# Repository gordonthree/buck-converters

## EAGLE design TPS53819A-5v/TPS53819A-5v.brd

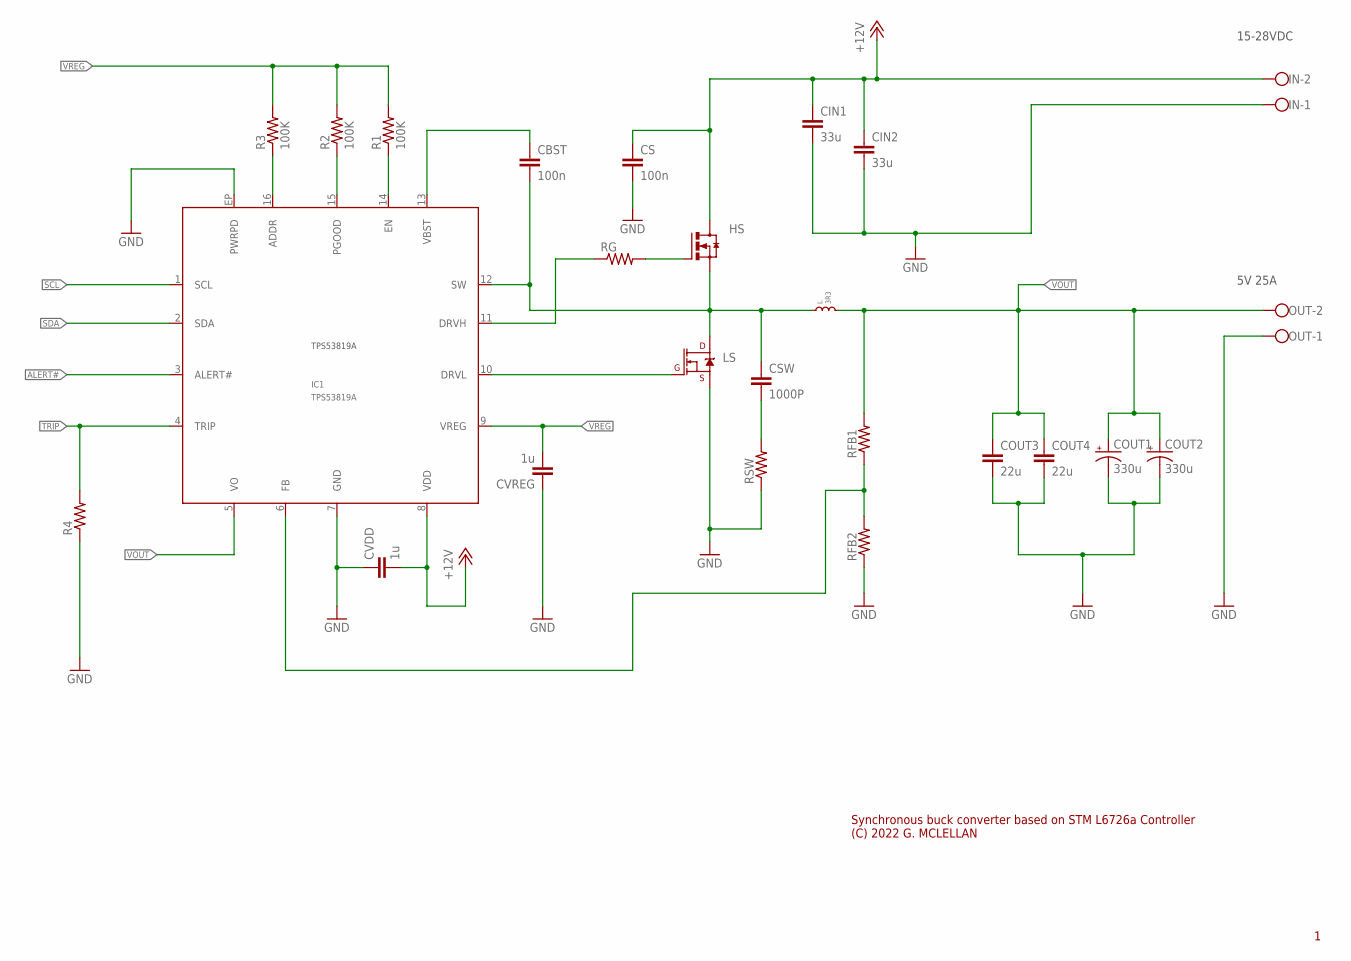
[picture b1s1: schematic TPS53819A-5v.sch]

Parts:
CBST: 100n; C0603
CIN1, CIN2: 33u; C2220K
COUT1, COUT2: 330u; SANYO-OSCON_SMD_C6
COUT3, COUT4: 22u; C1206
CS: 100n; C0805
CSW: 1000P; C0603
CVDD: 1u; C0805
CVREG: 1u; C0603
HS: N_MOSFET_POWERSO8; POWERSO8
IC1: TPS53819A; QFN-16
IN: W237-102
L: 3R3; XAL1010
LS: MOSFET-NCH-FDS6630A; SO08
OUT: W237-102
R1, R2, R3: 100K; R0603
R4: R-US_R0603; R0603
RFB1, RFB2: R-US_R0805; R0805
RG: R-US_R0603; R0603
RSW: R-US_R0603; R0603

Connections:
ADDR: IC1.16 (ADDR), R3.1
ALERT#: IC1.3 (ALERT#)
DRVH: HS.4 (G), RG.2
DRVH`: IC1.11 (DRVH), RG.1
DRVL: IC1.10 (DRVL), LS.4 (G)
EN: IC1.14 (EN), R1.1
FB: IC1.6 (FB), RFB1.1, RFB2.2
GND: CIN1.2, CIN2.2, COUT1.-, COUT2.-, COUT3.2, COUT4.2, CS.2, CVDD.1, CVREG.1, IC1.7 (GND), IC1.EP (PWRPD), IN.1, LS.1 (S), LS.2 (S), LS.3 (S), OUT.1, R4.1, RFB2.1, RSW.1
unnamed: CSW.2, RSW.2
PGOOD: IC1.15 (PGOOD), R2.1
SCL: IC1.1 (SCL)
SDA: IC1.2 (SDA)
SW: CBST.2, CSW.1, HS.1 (S), HS.2 (S), HS.3 (S), IC1.12 (SW), L.P$1 (1), LS.5 (D), LS.6 (D), LS.7 (D), LS.8 (D)
TRIP: IC1.4 (TRIP), R4.2
VBST: CBST.1, IC1.13 (VBST)
VDD: CIN1.1, CIN2.1, CS.1, CVDD.2, HS.5 (D), HS.6 (D), HS.7 (D), HS.8 (D), HS.PAD (D), IC1.8 (VDD), IN.2
VOUT: COUT1.+, COUT2.+, COUT3.1, COUT4.1, IC1.5 (VO), L.P$2 (2), OUT.2, RFB1.2
VREG: CVREG.2, IC1.9 (VREG), R1.2, R2.2, R3.2

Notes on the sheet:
Synchronous buck converter based on STM L6726a Controller (C) 2022 G. MCLELLAN
15-28VDC
5V 25A

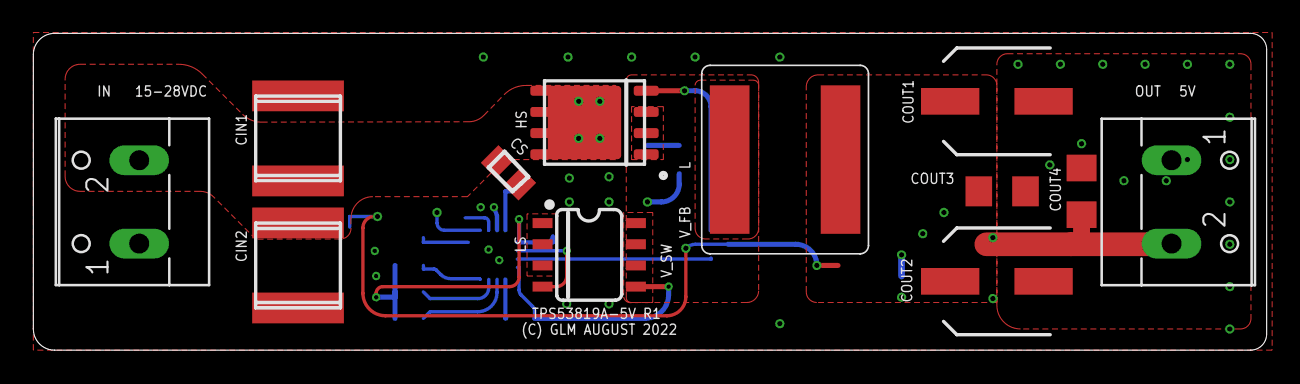
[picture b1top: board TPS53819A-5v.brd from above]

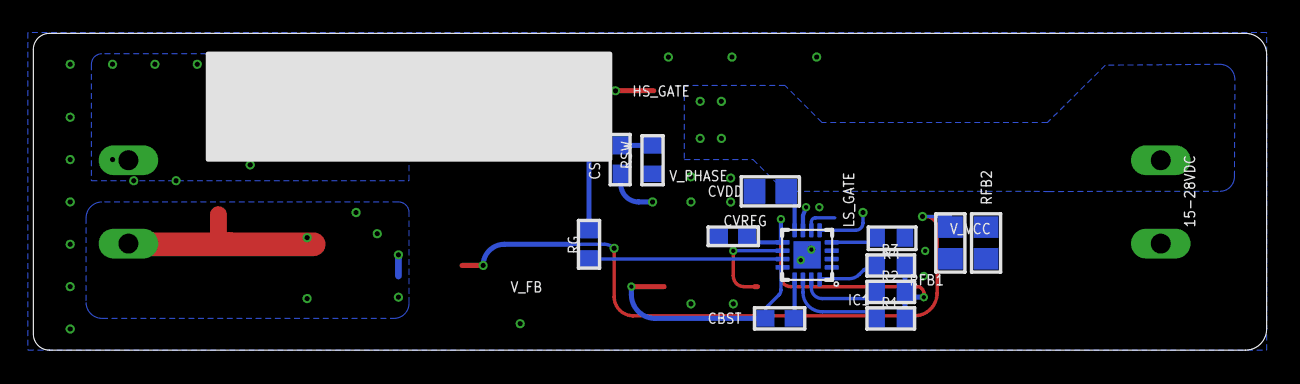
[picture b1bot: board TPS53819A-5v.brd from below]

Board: 2 copper layers, 74.0 x 19.0 mm, 25 parts (13 on the bottom side), 15 nets.

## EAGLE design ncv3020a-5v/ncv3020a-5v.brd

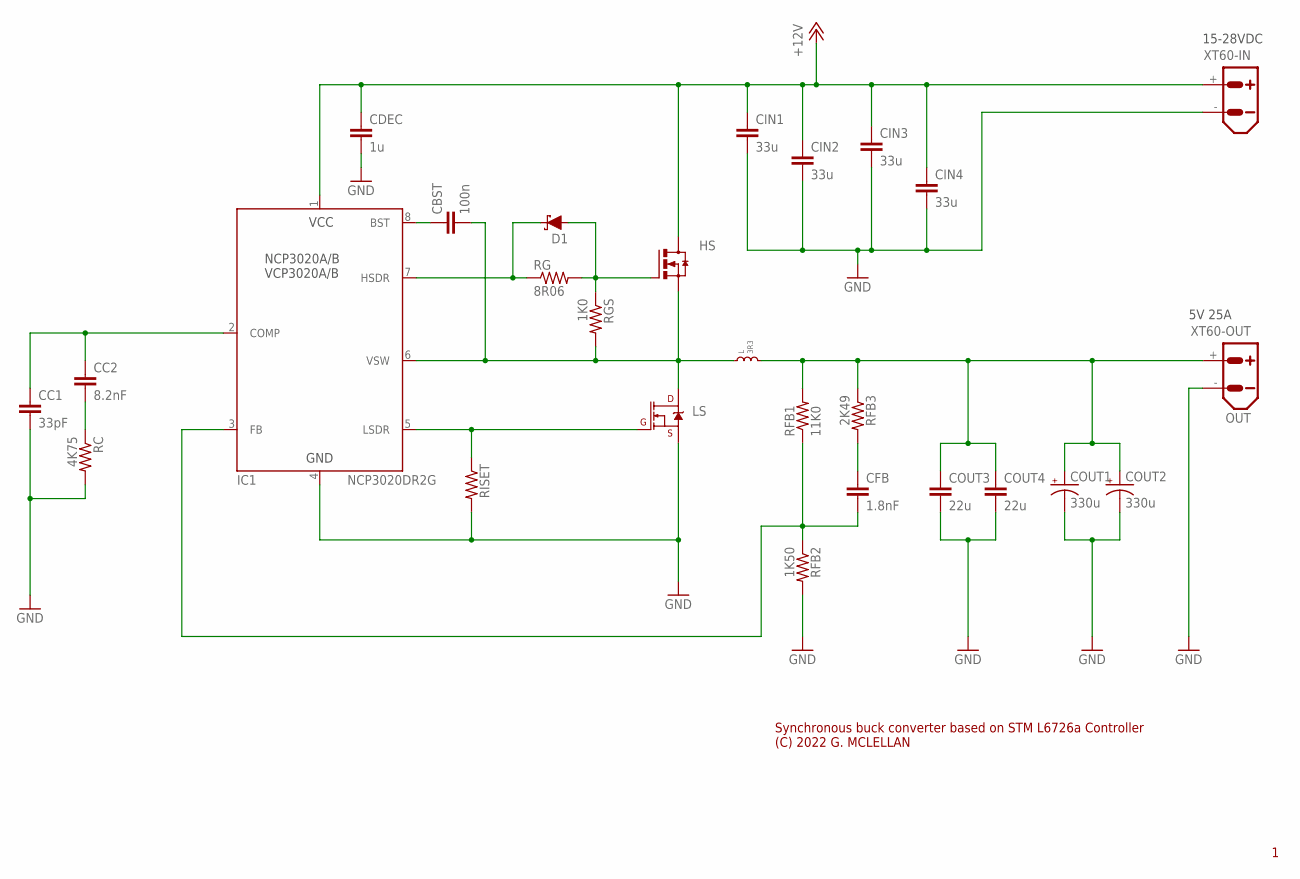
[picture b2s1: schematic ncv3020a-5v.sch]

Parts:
CBST: 100n; C0603
CC1: 33pF; C0603
CC2: 8.2nF; C0603
CDEC: 1u; C1206
CFB: 1.8nF; C0603
CIN1, CIN2, CIN3, CIN4: 33u; C2220K
COUT1, COUT2: 330u; SANYO-OSCON_SMD_C6
COUT3, COUT4: 22u; C1206
D1: DIODE-SCHOTTKY-BAT20J; SOD-323
HS: N_MOSFET_POWERSO8; POWERSO8
IC1: NCP3020DR2G; SO-08
L: 3R3; XAL1010
LS: MOSFET-NCH-FDS6630A; SO08
RC: 4K75; R0603
RFB1: 11K0; R0805
RFB2: 1K50; R0805
RFB3: 2K49; R0805
RG: 8R06; R0603
RGS: 1K0; R0603
RISET: R-US_R0603; R0603
XT60-IN: XT60PW-M
XT60-OUT: OUT; XT60PW-M

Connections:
CC1: CC2.2, RC.1
COMP: CC1.1, CC2.1, IC1.2 (COMP)
FB: CFB.2, IC1.3 (FB), RFB1.1, RFB2.1
GND: CC1.2, CDEC.2, CIN1.2, CIN2.2, CIN3.2, CIN4.2, COUT1.-, COUT2.-, COUT3.2, COUT4.2, IC1.4 (GND), LS.1 (S), LS.2 (S), LS.3 (S), RC.2, RFB2.2, RISET.2, XT60-IN.-, XT60-OUT.-
HSDR: D1.A, HS.4 (G), RG.2, RGS.1
HSDR`: D1.C, IC1.7 (HSDR), RG.1
LSDR: IC1.5 (LSDR), LS.4 (G), RISET.1
unnamed: CBST.1, IC1.8 (BST)
unnamed: CFB.1, RFB3.2
VCC: CDEC.1, CIN1.1, CIN2.1, CIN3.1, CIN4.1, HS.5 (D), HS.6 (D), HS.7 (D), HS.8 (D), HS.PAD (D), IC1.1 (VCC), XT60-IN.+
VOUT: COUT1.+, COUT2.+, COUT3.1, COUT4.1, L.P$2 (2), RFB1.2, RFB3.1, XT60-OUT.+
VSW: CBST.2, HS.1 (S), HS.2 (S), HS.3 (S), IC1.6 (VSW), L.P$1 (1), LS.5 (D), LS.6 (D), LS.7 (D), LS.8 (D), RGS.2

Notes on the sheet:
Synchronous buck converter based on STM L6726a Controller (C) 2022 G. MCLELLAN
15-28VDC
5V 25A

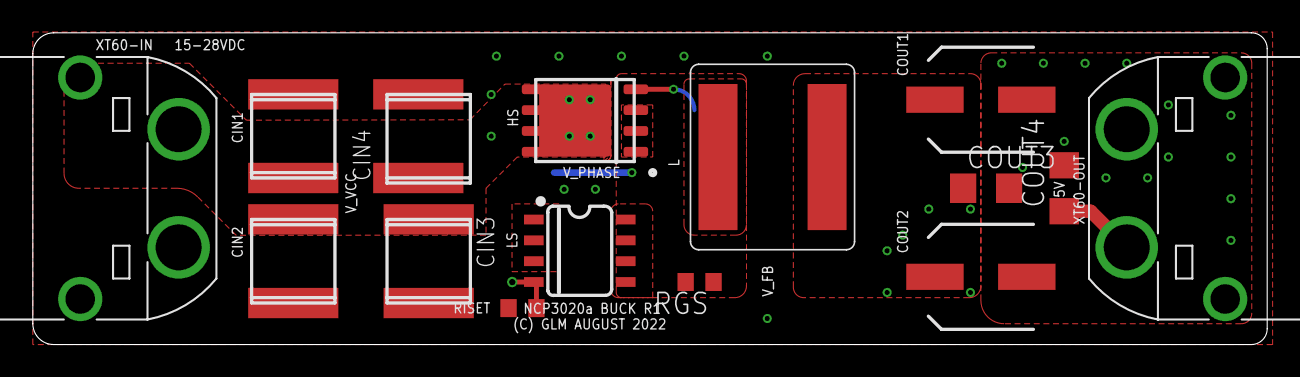
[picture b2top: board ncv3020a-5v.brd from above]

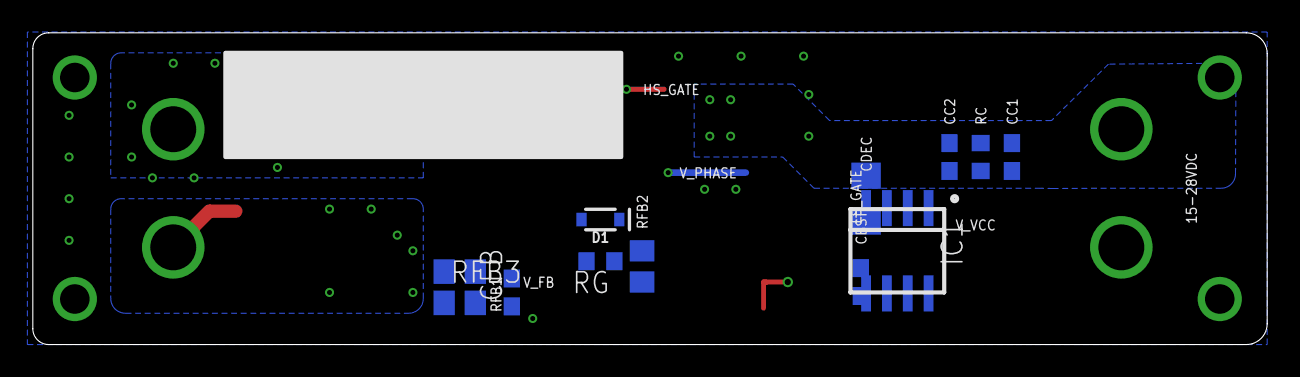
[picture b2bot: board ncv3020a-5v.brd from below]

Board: 2 copper layers, 75.2 x 19.0 mm, 27 parts (12 on the bottom side), 12 nets.

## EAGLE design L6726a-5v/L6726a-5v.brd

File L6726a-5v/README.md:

# L672Ga-5v R1

28v to 5v buck converter based on STM L6726a switchmode controller. Intended for use with 5s-6s LiFe chemistry battery packs.

Board shared [here](https://oshpark.com/shared_projects/CjUo6agw) at Osh Park ... I recommend 2oz copper.

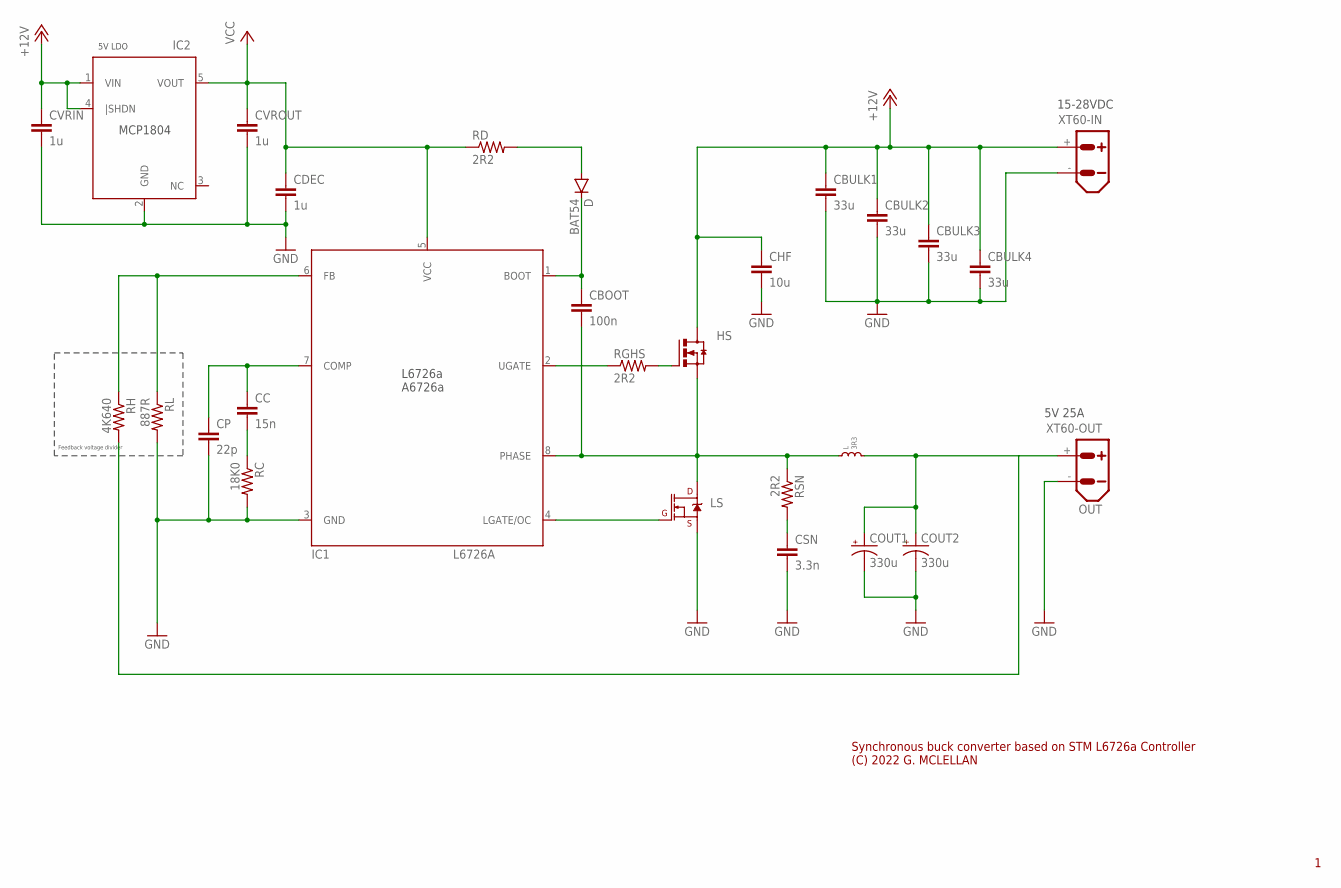
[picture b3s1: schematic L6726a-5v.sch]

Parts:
CBOOT: 100n; C0805
CBULK1, CBULK2, CBULK3, CBULK4: 33u; C2220K
CC: 15n; C0603
CDEC: 1u; C0603
CHF: 10u; C1206
COUT1, COUT2: 330u; SANYO-OSCON_SMD_C6
CP: 22p; C0603
CSN: 3.3n; C0603
CVRIN: 1u; C0603
CVROUT: 1u; C0603
D: BAT54; SOD-123
HS: N_MOSFET_POWERSO8; POWERSO8
IC1: L6726A; SO-08
IC2: MCP1804; SOT23-5
L: 3R3; XAL1010
LS: MOSFET-NCH-FDS6630A; SO08
RC: 18K0; R0603
RD: 2R2; R0603
RGHS: 2R2; R0805
RH: 4K640; R0805
RL: 887R; R0805
RSN: 2R2; R0603
XT60-IN: XT60PW-M
XT60-OUT: OUT; XT60PW-M

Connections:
+12V: CBULK1.1, CBULK2.1, CBULK3.1, CBULK4.1, CHF.1, CVRIN.1, HS.5 (D), HS.6 (D), HS.7 (D), HS.8 (D), HS.PAD (D), IC2.1 (VIN), IC2.4 (|SHDN), XT60-IN.+
BOOT: CBOOT.1, D.C, IC1.1 (BOOT)
CC: CC.2, RC.1
COMP: CC.1, CP.1, IC1.7 (COMP)
FB: IC1.6 (FB), RH.1, RL.1
GND: CBULK1.2, CBULK2.2, CBULK3.2, CBULK4.2, CDEC.2, CHF.2, COUT1.-, COUT2.-, CP.2, CSN.2, CVRIN.2, CVROUT.2, IC1.3 (GND), IC2.2 (GND), LS.1 (S), LS.2 (S), LS.3 (S), RC.2, RL.2, XT60-IN.-, XT60-OUT.-
LGATE: IC1.4 (LGATE/OC), LS.4 (G)
unnamed: D.A, RD.2
PHASE: CBOOT.2, HS.1 (S), HS.2 (S), HS.3 (S), IC1.8 (PHASE), L.P$1 (1), LS.5 (D), LS.6 (D), LS.7 (D), LS.8 (D), RSN.1
RSN: CSN.1, RSN.2
UGATE: HS.4 (G), RGHS.2
UGATE`: IC1.2 (UGATE), RGHS.1
VCC: CDEC.1, CVROUT.1, IC1.5 (VCC), IC2.5 (VOUT), RD.1
VOUT: COUT1.+, COUT2.+, L.P$2 (2), RH.2, XT60-OUT.+

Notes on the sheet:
Synchronous buck converter based on STM L6726a Controller (C) 2022 G. MCLELLAN
15-28VDC
5V 25A
Feedback voltage divider
5V LDO

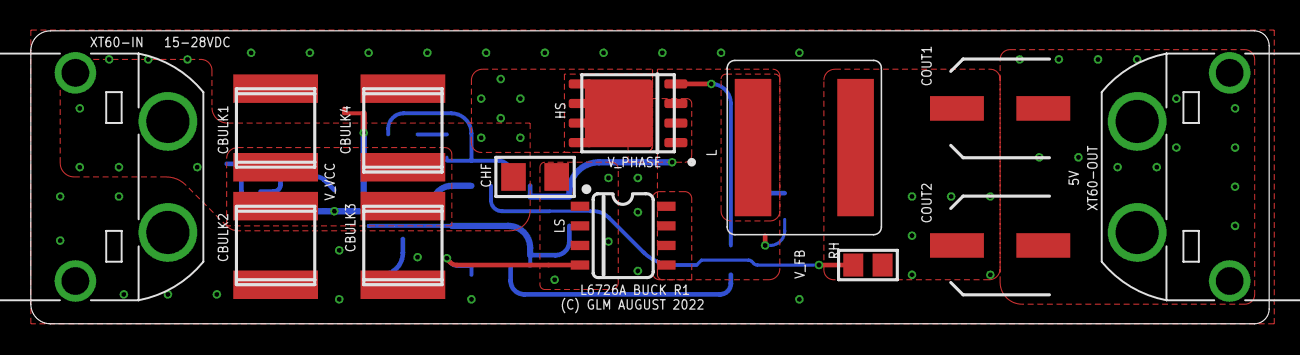
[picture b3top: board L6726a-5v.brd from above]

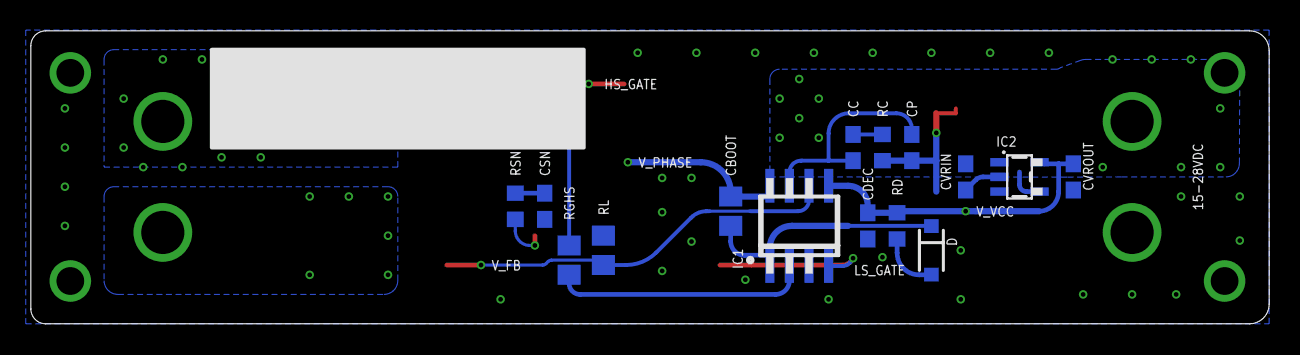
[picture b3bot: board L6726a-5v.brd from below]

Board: 2 copper layers, 80.3 x 19.0 mm, 28 parts (15 on the bottom side), 14 nets.

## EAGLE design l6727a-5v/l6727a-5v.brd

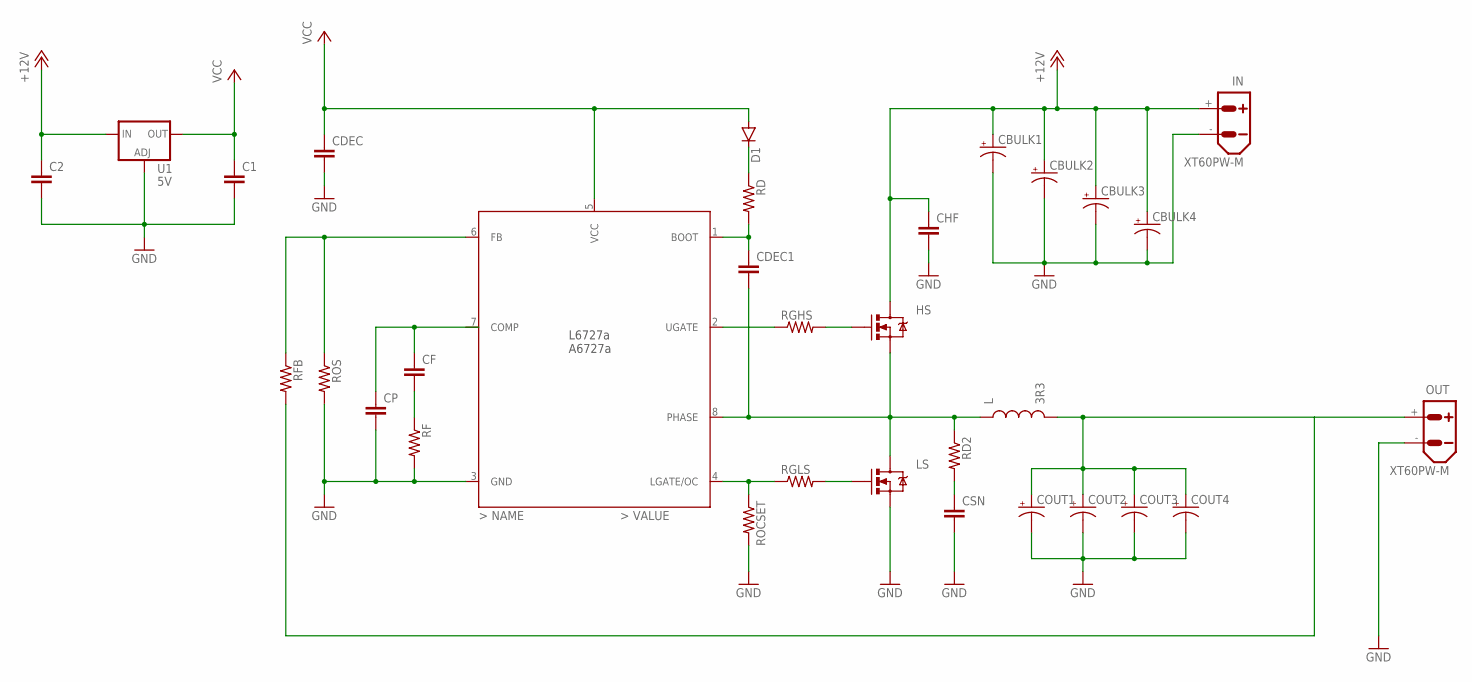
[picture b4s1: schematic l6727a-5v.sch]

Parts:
C1, C2: C-EUC1206; C1206
CBULK1, CBULK2, CBULK3, CBULK4: CPOL-USSANYO_SMD_E7; SANYO-OSCON_SMD_E7
CDEC, CDEC1: C-EUC1206; C1206
CF: C-EUC1206; C1206
CHF: C-EUC1206; C1206
COUT1, COUT2, COUT3, COUT4: CPOL-USSANYO_SMD_E7; SANYO-OSCON_SMD_E7
CP: C-EUC1206; C1206
CSN: C-EUC1206; C1206
D1: DIODESOD123; SOD-123
HS: MOSFET-NCHANNELFDS6630A; SO08
IC1: L6727A; SO-08
IN: XT60PW-M
L: 3R3; INDUCTOR_SDR1307
LS: MOSFET-NCHANNELFDS6630A; SO08
OUT: XT60PW-M
RD, RD2: R-US_R0603; R0603
RF: R-US_R0603; R0603
RFB: R-US_R0603; R0603
RGHS: R-US_R0603; R0603
RGLS: R-US_R0603; R0603
ROCSET: R-US_R0603; R0603
ROS: R-US_R0603; R0603
U1: 5V; SOT223

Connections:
+12V: C2.1, CBULK1.+, CBULK2.+, CBULK3.+, CBULK4.+, CHF.1, HS.5 (D), HS.6 (D), HS.7 (D), HS.8 (D), IN.+, U1.3 (IN)
COMP: CF.1, CP.1
FB: IC1.6 (FB), RFB.1, ROS.1
GND: C1.2, C2.2, CBULK1.-, CBULK2.-, CBULK3.-, CBULK4.-, CDEC.2, CHF.2, COUT1.-, COUT2.-, COUT3.-, COUT4.-, CP.2, CSN.2, IC1.3 (GND), IN.-, LS.1 (S), LS.2 (S), LS.3 (S), OUT.-, RF.2, ROCSET.2, ROS.2, U1.1 (ADJ)
LGATE: LS.4 (G), RGLS.2
LGATE`: IC1.4 (LGATE/OC), RGLS.1, ROCSET.1
unnamed: D1.C, RD.1
unnamed: CDEC1.1, IC1.1 (BOOT), RD.2
unnamed: CF.2, RF.1
PHASE: CDEC1.2, HS.1 (S), HS.2 (S), HS.3 (S), IC1.8 (PHASE), L.P$1 (1), LS.5 (D), LS.6 (D), LS.7 (D), LS.8 (D), RD2.1
RSN: CSN.1, RD2.2
UGATE: HS.4 (G), RGHS.2
UGATE`: IC1.2 (UGATE), RGHS.1
VCC: C1.1, CDEC.1, D1.A, IC1.5 (VCC), U1.2 (OUT)
VOUT: COUT1.+, COUT2.+, COUT3.+, COUT4.+, L.P$2 (2), OUT.+, RFB.2

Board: 2 copper layers, 32 parts (3 on the bottom side), 15 nets, no tracks yet.

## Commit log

2022-08-28 created new parts libraries
2022-08-28 added some docs
2022-08-28 added docs
2022-08-28 initial schematic, started rough layout
2022-08-28 increased symbol size
2022-08-28 updated ignore file
2022-08-29 renamed files and folders, layout mostly complete
2022-08-29 lots of progress with routing, verifying component packages
2022-08-29 changed mosfet package, blew up layout
2022-08-30 update used libraries
2022-08-30 add empty project files
2022-08-30 finished routing transistors, still need LDO
2022-08-30 a few more tweaks
2022-08-30 finalized layout, I think I'm happy
2022-08-30 Microchip MCP1804 ldo vreg
2022-08-30 finishing touches
2022-08-30 Added empty project file
2022-08-30 let the ground pour through between inductor
2022-08-30 a few more tweaks!
2022-08-30 corrected some minor library errors
2022-08-30 added schematic pdf
2022-08-30 created readme for l6726a project
2022-08-31 removed pdf schematic, added png schematic
2022-08-31 top and bottom renders from Oshpark.com
2022-08-31 updated DRU rules from Osh Park, finale tweaks to layout
2022-08-31 started work on layout for ncv3020 chip
2022-09-08 created new library
2022-09-08 added for reference
2022-09-08 initial layout, copied from previous designs
2022-09-09 made progress on routing, missing i2c connector still

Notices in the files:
parts and their libraries:
SparkFun-DiscreteSemi: Licensing: Creative Commons ShareAlike 4.0 International - https://creativecommons.org/licenses/by-sa/4.0
